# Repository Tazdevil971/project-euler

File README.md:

# Project Euler
Project euler is an open-source bluetooth head tracker module.

## Folder structure
- `/`: main source code
- `/docs/`: documentation, pin definitions and pinouts.
- `/pcb/`: kicad PCB project

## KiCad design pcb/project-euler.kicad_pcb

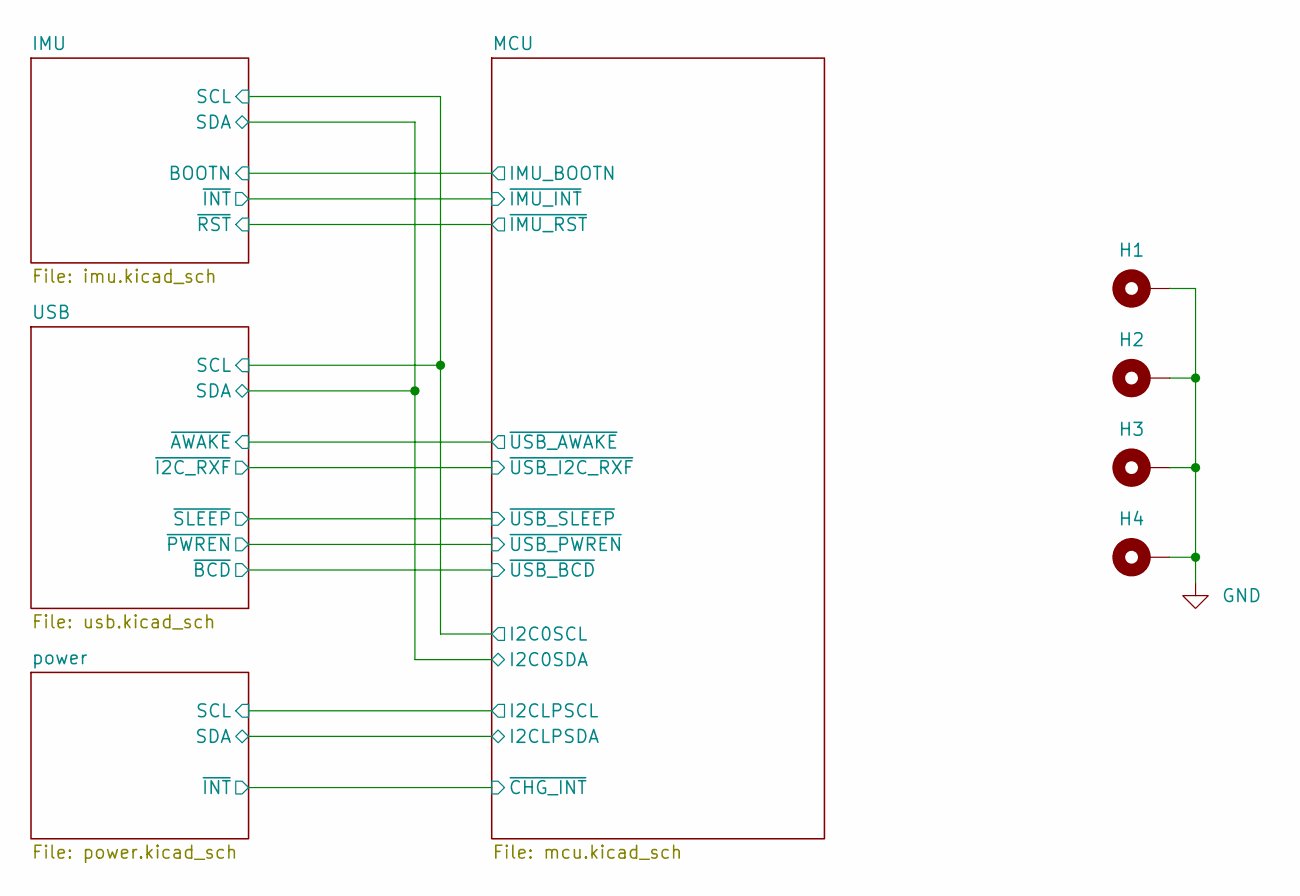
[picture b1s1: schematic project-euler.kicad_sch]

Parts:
H1, H2, H3, H4: M2; MountingHole_2.7mm_M2.5_Pad

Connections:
GND: H1.1, H2.1, H3.1, H4.1; also elsewhere on the board

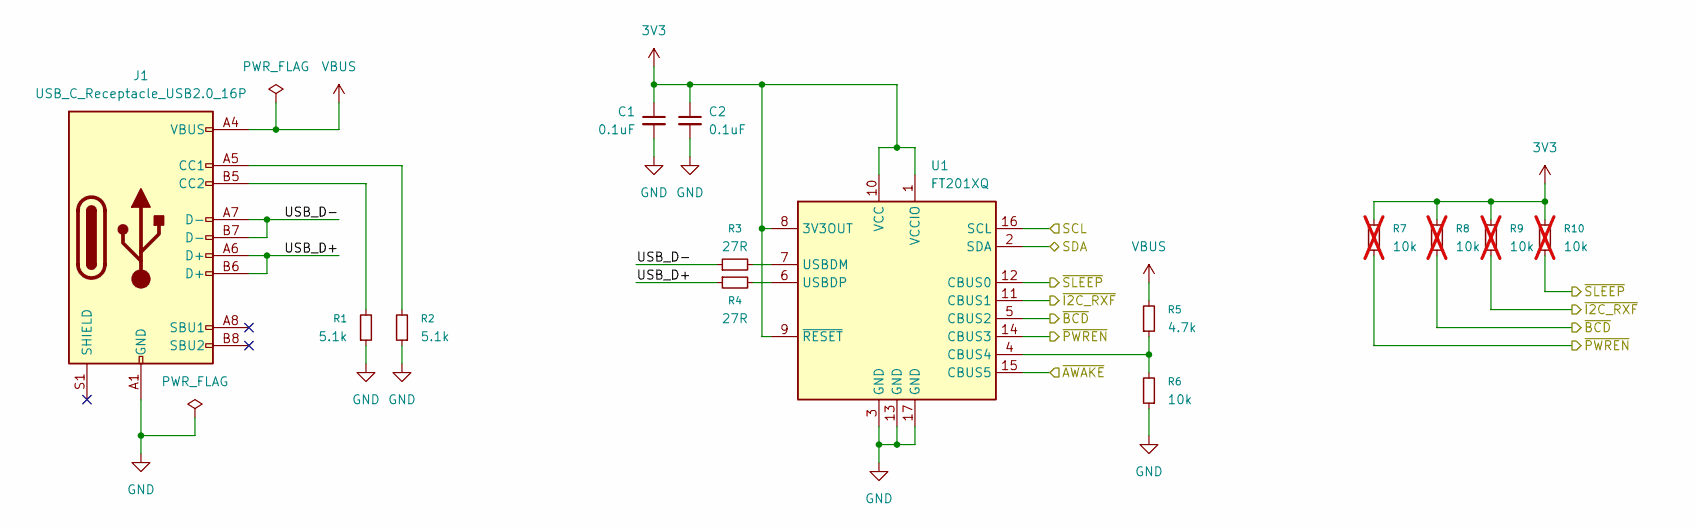
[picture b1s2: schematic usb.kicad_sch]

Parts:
C1, C2: 0.1uF; C_0603_1608Metric; Part NO GCJ188R71H104KA12D
J1: USB_C_Receptacle_USB2.0_16P; USB_C_Receptacle_GCT_USB4105-xx-A_16P_TopMnt_Horizontal; Part NO USB4105
R1, R2: 5.1k; R_0603_1608Metric_Pad0.98x0.95mm_HandSolder; Part NO CRCW06035K10FKEBC
R3, R4: 27R; R_0603_1608Metric; Part NO CRCW060327R0FKEAC
R5: 4.7k; R_0603_1608Metric; Part NO CRCW06034K70FKEC
R6: 10k; R_0603_1608Metric; Part NO CRCW060310K0FKECC
R7, R8, R9, R10: 10k; R_0603_1608Metric_Pad0.98x0.95mm_HandSolder; Part NO CRCW060310K0FKECC; not fitted
U1: FT201XQ; QFN-16-1EP_4x4mm_P0.65mm_EP2.1x2.1mm; Part NO FT201XQ

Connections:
3V3: C1.1, C2.1, R7.2, R8.2, R9.2, R10.2, U1.1 (VCCIO), U1.8 (3V3OUT), U1.9 (~RESET), U1.10 (VCC); also elsewhere on the board
/IMU/SCL: U1.16 (SCL); also elsewhere on the board
/IMU/SDA: U1.2 (SDA); also elsewhere on the board
/MCU/~USB_AWAKE: U1.15 (CBUS5); also elsewhere on the board
/MCU/~USB_BCD: R8.1, U1.5 (CBUS2); also elsewhere on the board
/MCU/~USB_I2C_RXF: R9.1, U1.11 (CBUS1); also elsewhere on the board
/MCU/~USB_PWREN: R7.1, U1.14 (CBUS3); also elsewhere on the board
/MCU/~USB_SLEEP: R10.1, U1.12 (CBUS0); also elsewhere on the board
/USB/USB_D+: J1.A6 (D+), J1.B6 (D+), R4.1
/USB/USB_D-: J1.A7 (D-), J1.B7 (D-), R3.1
GND: C1.2, C2.2, J1.A1 (GND), J1.A12 (GND), J1.B1 (GND), J1.B12 (GND), R1.1, R2.1, R6.1, U1.3 (GND), U1.13 (GND), U1.17 (GND); also elsewhere on the board
unnamed: J1.A5 (CC1), R2.2
unnamed: J1.B5 (CC2), R1.2
unnamed: R5.1, R6.2, U1.4 (CBUS4)
unnamed: R3.2, U1.7 (USBDM)
unnamed: R4.2, U1.6 (USBDP)
VBUS: J1.A4 (VBUS), J1.A9 (VBUS), J1.B4 (VBUS), J1.B9 (VBUS), R5.2; also elsewhere on the board

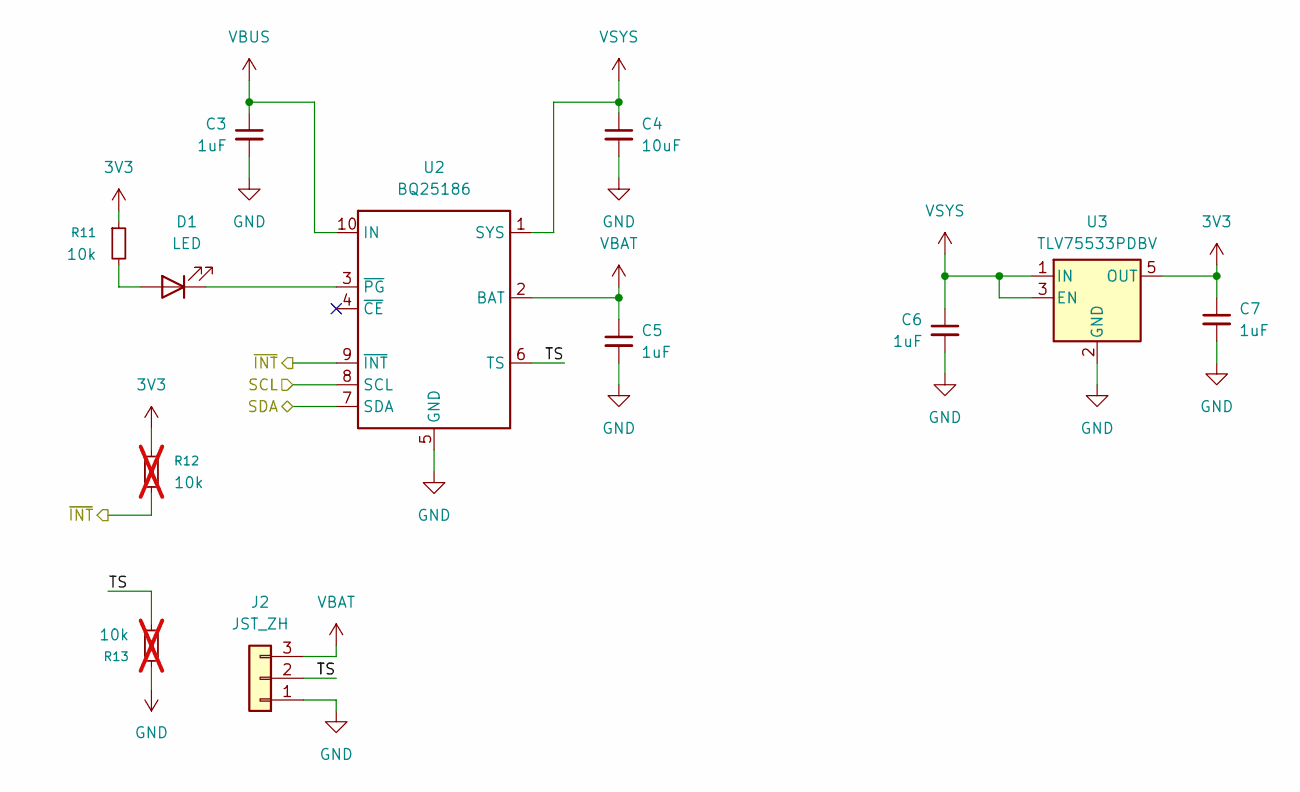
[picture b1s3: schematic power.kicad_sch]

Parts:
C3, C5, C6, C7: 1uF; C_0603_1608Metric; Part NO GRM188R61A105KA61D
C4: 10uF; C_0603_1608Metric; Part NO GRM188R60G106ME47J
D1: LED; LED_0603_1608Metric_Pad1.05x0.95mm_HandSolder; Part NO 150060GS75000
J2: JST_ZH; JST_ZH_B3B-ZR_1x03_P1.50mm_Vertical; Part NO B3B-ZR
R11: 10k; R_0603_1608Metric; Part NO CRCW060310K0FKECC
R12, R13: 10k; R_0603_1608Metric_Pad0.98x0.95mm_HandSolder; Part NO CRCW060310K0FKECC; not fitted
U2: BQ25186; Texas_DLH0010A_WSON-10-1EP_2.2x2mm_P0.4mm_EP0.9x1.5mm_Therm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; Part NO BQ25186
U3: TLV75533PDBV; SOT-23-5; Part NO TLV75533PDBV

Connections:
3V3: C7.1, R11.1, R12.1, U3.5 (OUT); also elsewhere on the board
/MCU/I2CLPSCL: U2.8 (SCL); also elsewhere on the board
/MCU/I2CLPSDA: U2.7 (SDA); also elsewhere on the board
/MCU/~CHG_INT: R12.2, U2.9 (~INT); also elsewhere on the board
/power/TS: J2.2, R13.2, U2.6 (TS)
GND: C3.2, C4.2, C5.2, C6.2, C7.2, J2.1, R13.1, U2.5 (GND), U2.11 (GND), U3.2 (GND); also elsewhere on the board
unnamed: D1.2 (A), R11.2
unnamed: D1.1 (K), U2.3 (~PG)
VBAT: C5.1, J2.3, U2.2 (BAT); also elsewhere on the board
VBUS: C3.1, U2.10 (IN); also elsewhere on the board
VSYS: C4.1, C6.1, U2.1 (SYS), U3.1 (IN), U3.3 (EN)

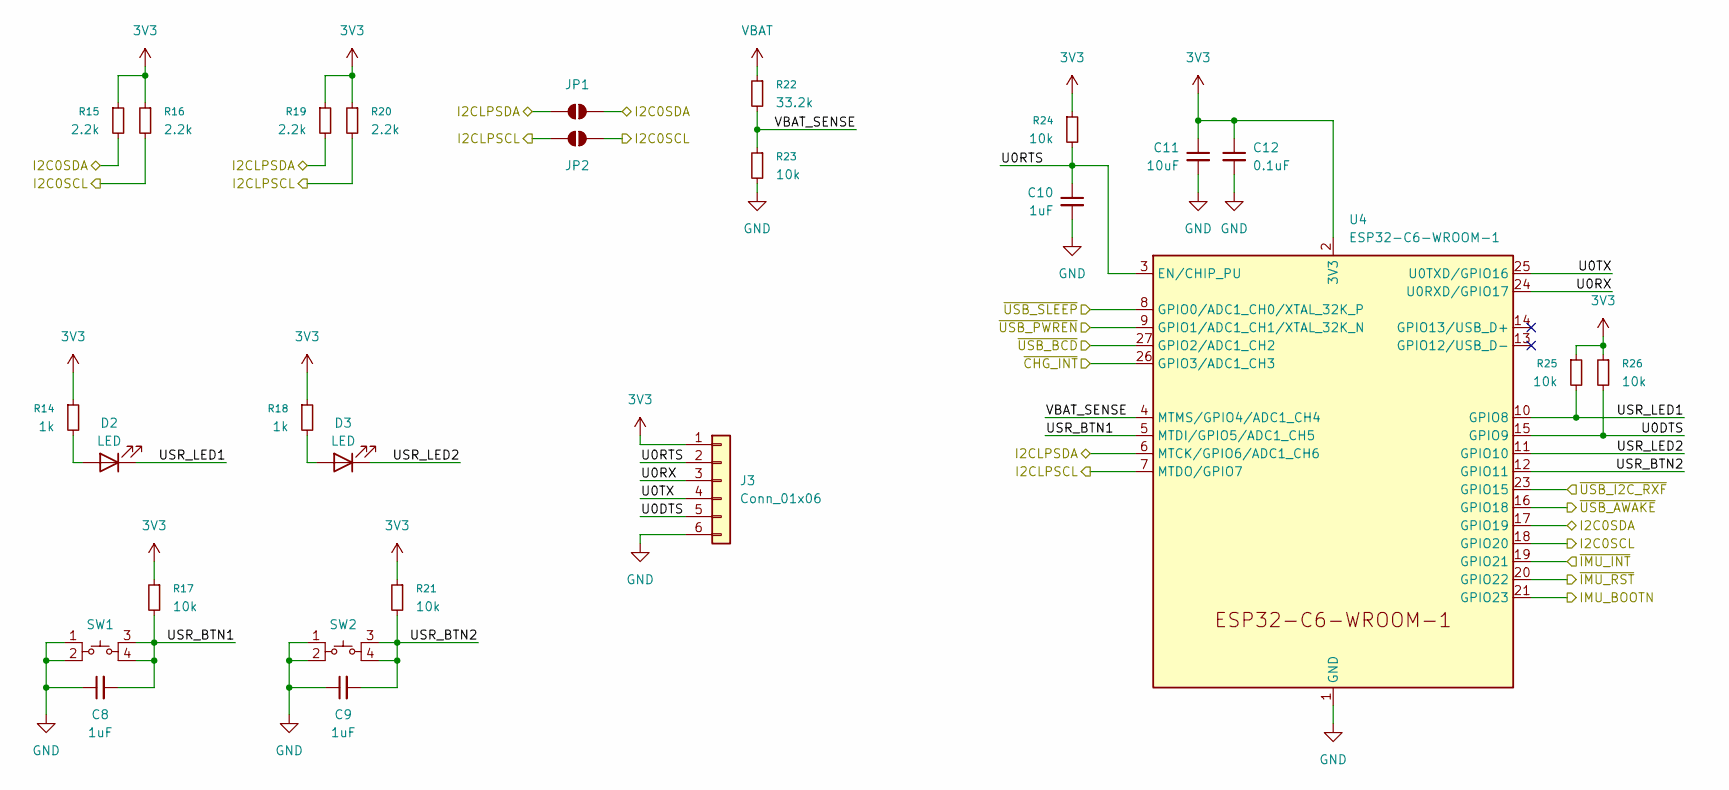
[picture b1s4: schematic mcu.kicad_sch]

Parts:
C8, C9, C10: 1uF; C_0603_1608Metric; Part NO GRM188R61A105KA61D
C11: 10uF; C_0603_1608Metric; Part NO GRM188R60G106ME47J
C12: 0.1uF; C_0603_1608Metric; Part NO GCJ188R71H104KA12D
D2, D3: LED; LED_0603_1608Metric_Pad1.05x0.95mm_HandSolder; Part NO 150060GS75000
J3: Conn_01x06; PinHeader_2x03_P2.54mm_Vertical
JP1, JP2: SolderJumper_2_Open; SolderJumper-2_P1.3mm_Open_Pad1.0x1.5mm
R14, R18: 1k; R_0603_1608Metric; Part NO CRCW06031K00FKECC
R15, R16: 2.2k; R_0603_1608Metric; Part NO CRCW06032K20FKEAC
R17, R21, R23, R24, R25, R26: 10k; R_0603_1608Metric; Part NO CRCW060310K0FKECC
R19, R20: 2.2k; R_0603_1608Metric_Pad0.98x0.95mm_HandSolder; Part NO CRCW06032K20FKEAC
R22: 33.2k; R_0603_1608Metric; Part NO CRCW060333K2FKEAC
SW1, SW2: SW_TL1105AF160Q; Part NO TL1105AF160Q
U4: ESP32-C6-WROOM-1; Part NO ESP32-C6-WROOM-1

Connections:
3V3: C11.1, C12.1, J3.1, R14.1, R15.1, R16.1, R17.1, R18.1, R19.1, R20.1, R21.1, R24.1, R25.1, R26.1, U4.2 (3V3); also elsewhere on the board
/IMU/BOOTN: U4.21 (GPIO23); also elsewhere on the board
/IMU/SCL: JP2.2 (B), R16.2, U4.18 (GPIO20); also elsewhere on the board
/IMU/SDA: JP1.2 (B), R15.2, U4.17 (GPIO19); also elsewhere on the board
/IMU/~INT: U4.19 (GPIO21); also elsewhere on the board
/IMU/~RST: U4.20 (GPIO22); also elsewhere on the board
/MCU/I2CLPSCL: JP2.1 (A), R20.2, U4.7 (MTDO/GPIO7); also elsewhere on the board
/MCU/I2CLPSDA: JP1.1 (A), R19.2, U4.6 (MTCK/GPIO6/ADC1_CH6); also elsewhere on the board
/MCU/U0DTS: J3.5, R26.2, U4.15 (GPIO9)
/MCU/U0RTS: C10.1, J3.2, R24.2, U4.3 (EN/CHIP_PU)
/MCU/U0RX: J3.3, U4.24 (U0RXD/GPIO17)
/MCU/U0TX: J3.4, U4.25 (U0TXD/GPIO16)
/MCU/USR_BTN1: C8.2, R17.2, SW1.3, SW1.4, U4.5 (MTDI/GPIO5/ADC1_CH5)
/MCU/USR_BTN2: C9.2, R21.2, SW2.3, SW2.4, U4.12 (GPIO11)
/MCU/USR_LED1: D2.1 (K), R25.2, U4.10 (GPIO8)
/MCU/USR_LED2: D3.1 (K), U4.11 (GPIO10)
/MCU/VBAT_SENSE: R22.2, R23.1, U4.4 (MTMS/GPIO4/ADC1_CH4)
/MCU/~CHG_INT: U4.26 (GPIO3/ADC1_CH3); also elsewhere on the board
/MCU/~USB_AWAKE: U4.16 (GPIO18); also elsewhere on the board
/MCU/~USB_BCD: U4.27 (GPIO2/ADC1_CH2); also elsewhere on the board
/MCU/~USB_I2C_RXF: U4.23 (GPIO15); also elsewhere on the board
/MCU/~USB_PWREN: U4.9 (GPIO1/ADC1_CH1/XTAL_32K_N); also elsewhere on the board
/MCU/~USB_SLEEP: U4.8 (GPIO0/ADC1_CH0/XTAL_32K_P); also elsewhere on the board
GND: C8.1, C9.1, C10.2, C11.2, C12.2, J3.6, R23.2, SW1.1, SW1.2, SW2.1, SW2.2, U4.1 (GND), U4.28 (GND), U4.29 (GND); also elsewhere on the board
unnamed: D2.2 (A), R14.2
unnamed: D3.2 (A), R18.2
VBAT: R22.1; also elsewhere on the board

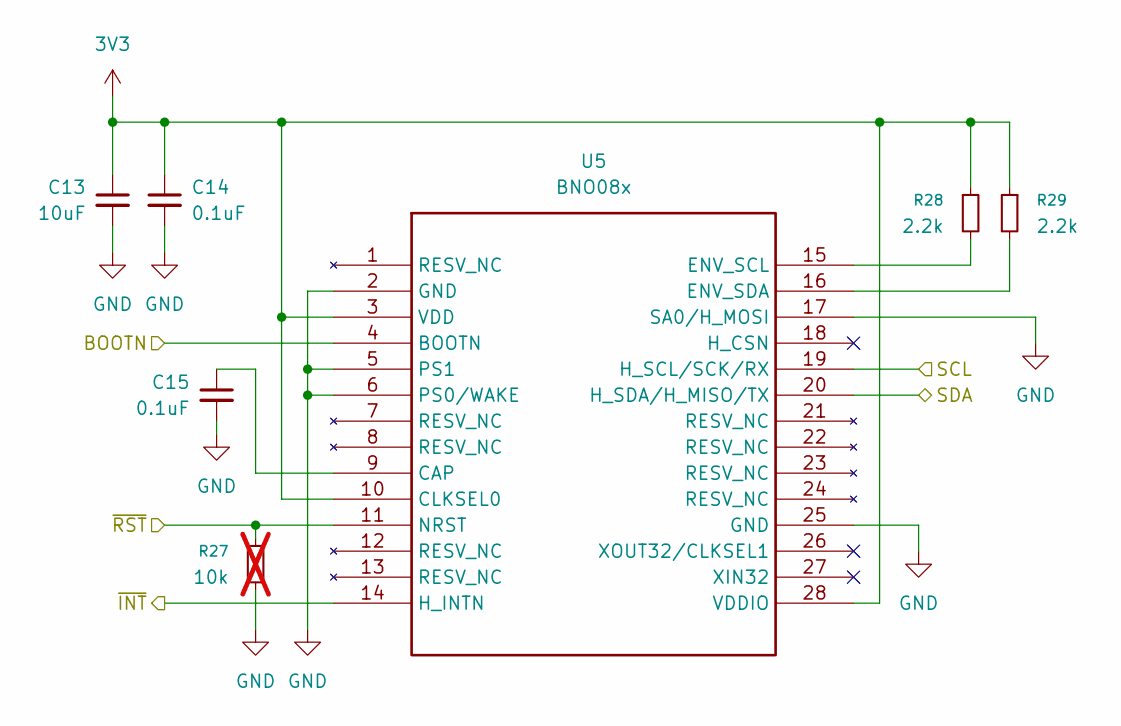
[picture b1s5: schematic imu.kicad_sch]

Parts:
C13: 10uF; C_0603_1608Metric; Part NO GRM188R60G106ME47J
C14, C15: 0.1uF; C_0603_1608Metric; Part NO GCJ188R71H104KA12D
R27: 10k; R_0603_1608Metric; Part NO CRCW060310K0FKECC; not fitted
R28, R29: 2.2k; R_0603_1608Metric; Part NO CRCW06032K20FKEAC
U5: BNO08x; LGA-28_5.2x3.8mm_P0.5mm; Part NO BNO086

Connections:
3V3: C13.1, C14.1, R28.1, R29.1, U5.3 (VDD), U5.10 (CLKSEL0), U5.28 (VDDIO); also elsewhere on the board
/IMU/BOOTN: U5.4 (BOOTN); also elsewhere on the board
/IMU/SCL: U5.19 (H_SCL/SCK/RX); also elsewhere on the board
/IMU/SDA: U5.20 (H_SDA/H_MISO/TX); also elsewhere on the board
/IMU/~INT: U5.14 (H_INTN); also elsewhere on the board
/IMU/~RST: R27.1, U5.11 (NRST); also elsewhere on the board
GND: C13.2, C14.2, C15.2, R27.2, U5.2 (GND), U5.5 (PS1), U5.6 (PS0/WAKE), U5.17 (SA0/H_MOSI), U5.25 (GND); also elsewhere on the board
unnamed: C15.1, U5.9 (CAP)
unnamed: R28.2, U5.15 (ENV_SCL)
unnamed: R29.2, U5.16 (ENV_SDA)

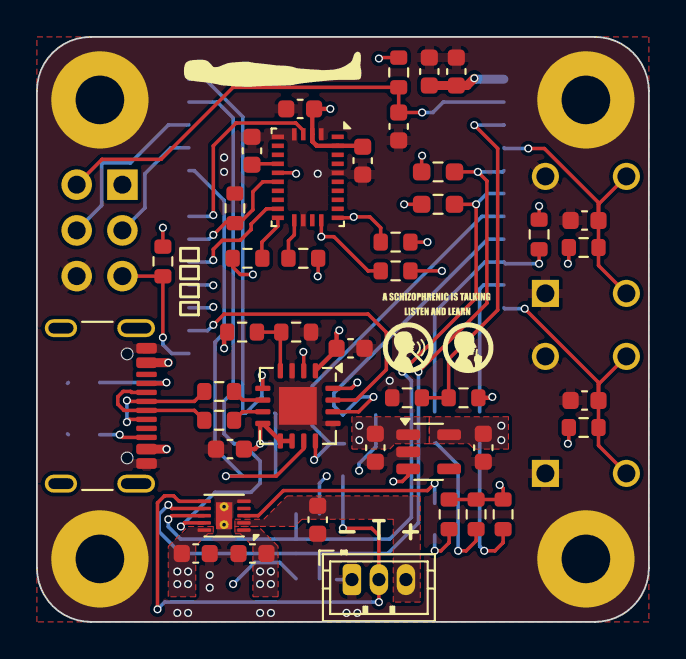
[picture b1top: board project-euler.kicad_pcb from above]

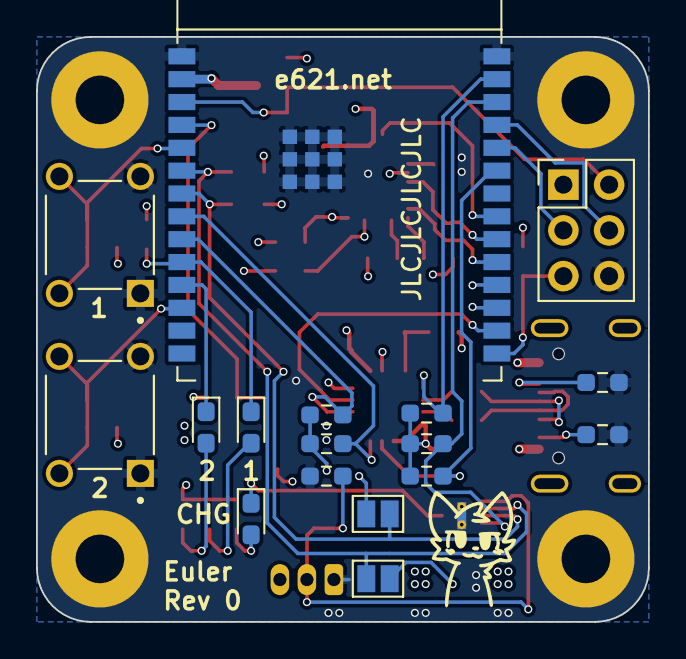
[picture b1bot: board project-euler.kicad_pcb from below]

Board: 4 copper layers, 34.0 x 32.5 mm, 63 parts (17 on the bottom side), 42 nets.

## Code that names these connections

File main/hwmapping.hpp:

#pragma once

#include <driver/gpio.h>
#include <driver/i2c_master.h>

namespace euler::hwmapping {

constexpr gpio_num_t USR_LED1 = GPIO_NUM_8;
constexpr gpio_num_t USR_LED2 = GPIO_NUM_10;

constexpr gpio_num_t USR_BTN1 = GPIO_NUM_5;
constexpr gpio_num_t USR_BTN2 = GPIO_NUM_11;

// constexpr adc_channel_t BAT_SENSE = ADC_CHANNEL_4;

constexpr gpio_num_t USB_SLEEP = GPIO_NUM_0;
constexpr gpio_num_t USB_PWREN = GPIO_NUM_1;
constexpr gpio_num_t USB_BCD = GPIO_NUM_2;
constexpr gpio_num_t USB_RXF = GPIO_NUM_15;
constexpr gpio_num_t USB_KEEP_AWAKE = GPIO_NUM_18;

constexpr gpio_num_t CHG_INT = GPIO_NUM_3;

constexpr gpio_num_t BNO_IRQ = GPIO_NUM_21;
constexpr gpio_num_t BNO_RESET = GPIO_NUM_22;
constexpr gpio_num_t BNO_BOOTN = GPIO_NUM_23;

constexpr gpio_num_t I2C_SDA = GPIO_NUM_19;
constexpr gpio_num_t I2C_SCL = GPIO_NUM_20;

constexpr gpio_num_t I2C_LP_SDA = GPIO_NUM_6;
constexpr gpio_num_t I2C_LP_SCL = GPIO_NUM_7;

}  // namespace euler::hwmapping

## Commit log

2025-11-09 [firmware/pcb] Initial firmware upload + fixed mistake in PCB + added errata documentation
2025-11-14 [firmware] Initial Bno08x driver taking shape
